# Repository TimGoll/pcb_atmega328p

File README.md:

# PCB Atmega328PB

The board's design is heavily based on the design of the Arduino Uno. All the USB communication stuff was removed. The board is therefore reduced to its bare minimum. The most notable deviation in comparison to the Arduino Uno is that my board uses a 20MHz crystal.

_(The schematic and the PCB I created from this schematic)_

The board is a two layer design with mostly ground planes that are stitched together with multiple vias. All the relevant parts are mounted to the front side.

_(The finished PCB aith the programmer next to it)_

The design of the board works like intended with the one issue, that the ISP connector is mirrored. This however is fixed in the current version in this repository.

## Setup

This board has to be programmed with an ISP connection located on the board. There are different programmers available, I'm using the [Pololu USB AVR Programmer v2.1](https://www.pololu.com/product/3172). The driver package should be installed as it comes with a nice tool to look at the programmer.

A working programmer looks something like this. Do note here that I'm using an external power supply for the MCU here.

If the board is connected, `avrdude` can be used to read the info of the MCU. Use `./avrdude.exe` in the command line while being in the correct folder, for me it is: `C:\Program Files (x86)\Arduino\hardware\tools\avr\bin`.

Use the following command to read the board information:

```sh
./avrdude.exe -C ../etc/avrdude.conf -c stk500 -P COM8 -b 19200 -p m328pb -v
```

`COM8` is used here because it is the programming port of this programmer, `stk500` is the type of the programmer. See [this article](http://www.s6z.de/cms/index.php/arduino/nuetzliches/31-usb-isp-programmer-fuer-atmel-avr-usbasp) for more information on this.

To use an external crystal, the fuses of the board have to be set. The fuse bits can be easily set with the [AVR fuse calculator](https://eleccelerator.com/fusecalc/fusecalc.php?chip=atmega328p&LOW=DE&HIGH=D9&EXTENDED=FF&LOCKBIT=FF). They then have to be flashed to the board. The command is mostly the same, only the `-v` gets replaced by the fuse byte command from the website.

Now the board can be flashed with the desired software. There are different ways to do this, but if the Arduino IDE should be used, a few things have to be set up.

First [MiniCore](https://github.com/MCUdude/MiniCore) has to be added as it features a few more missing AVRs with UI based configurability. The json file link had to be added in the Arduino Settings page as described in the project's readme.

These are the settings that were used here for this specific board setup. It can be easily verified by uploading a simple LED blink sketch.

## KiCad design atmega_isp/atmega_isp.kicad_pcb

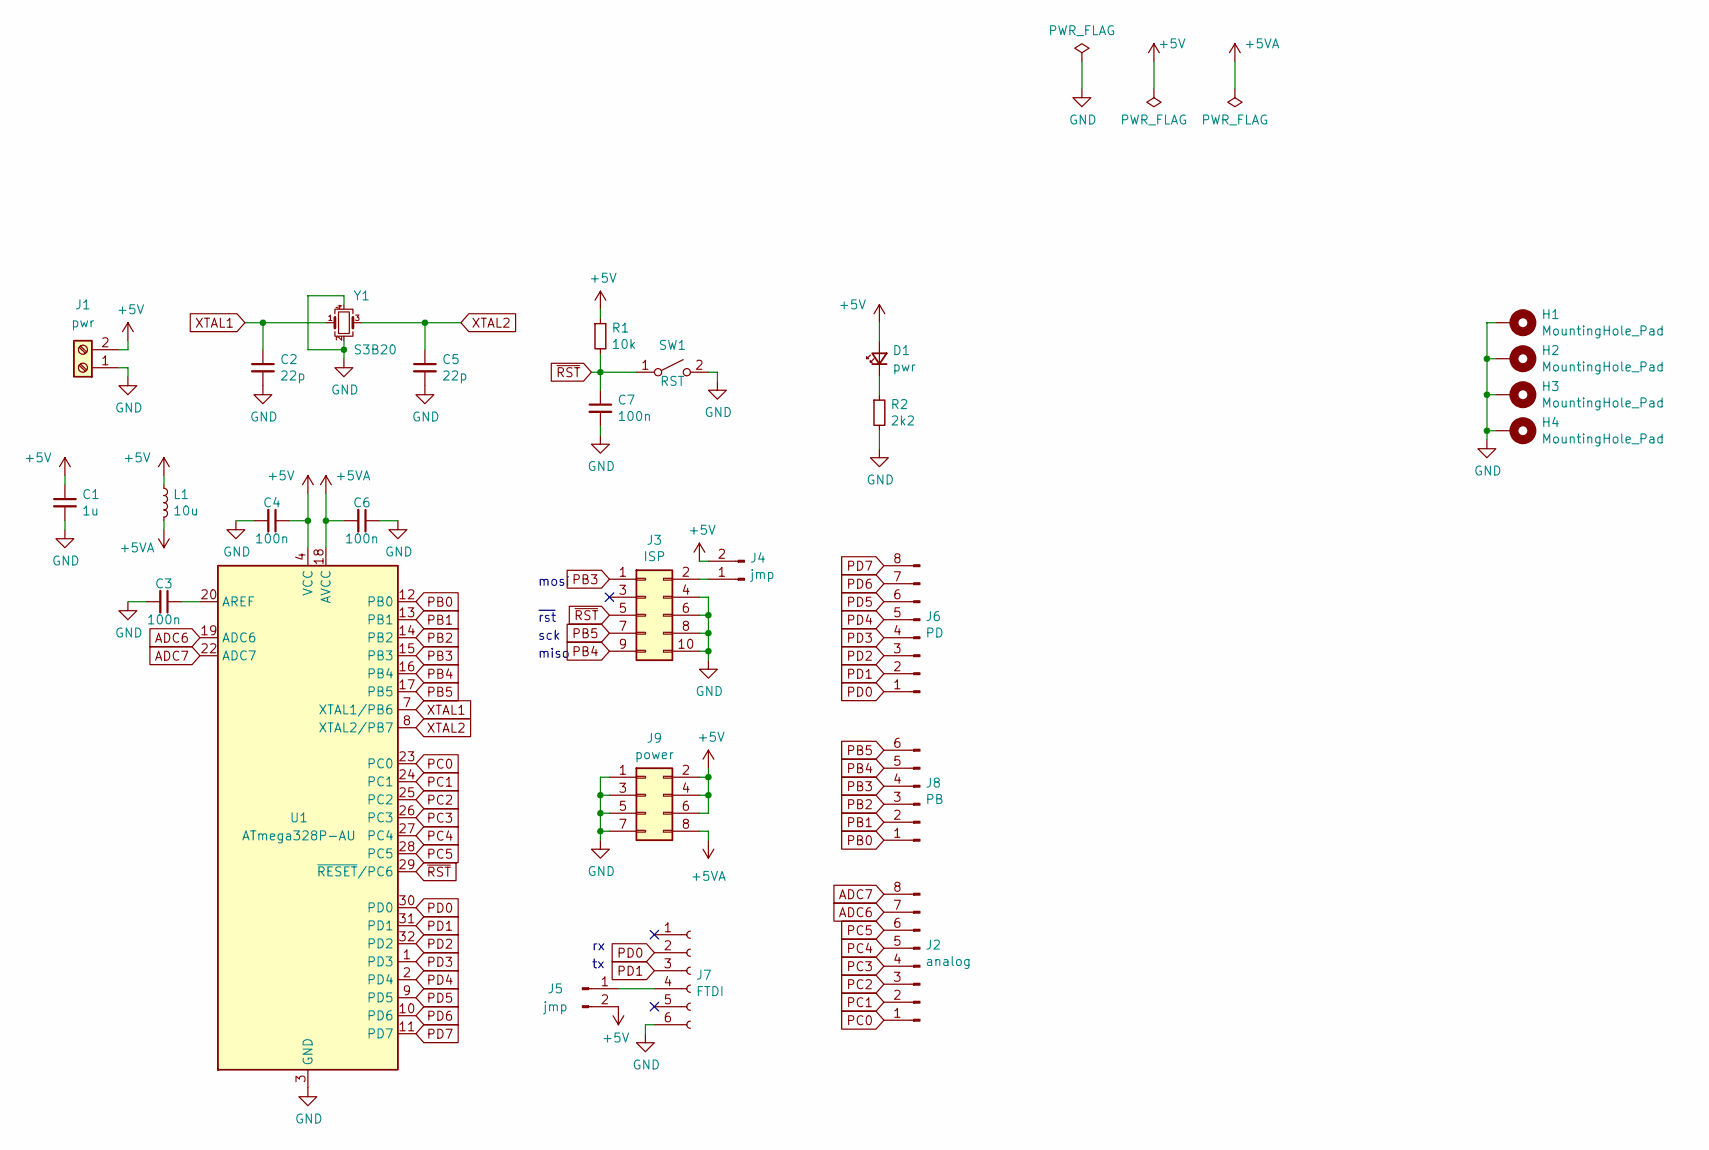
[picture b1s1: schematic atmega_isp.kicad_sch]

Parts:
C1: 1u; C_0805_2012Metric_Pad1.15x1.40mm_HandSolder
C2, C5: 22p; C_0805_2012Metric_Pad1.15x1.40mm_HandSolder
C3, C4, C6, C7: 100n; C_0805_2012Metric_Pad1.15x1.40mm_HandSolder
D1: pwr; LED_0805_2012Metric_Castellated
H1, H2, H3, H4: MountingHole_Pad; MountingHole_4.3mm_M4_Pad_Via
J1: pwr; TerminalBlock_Phoenix_MKDS-1,5-2-5.08_1x02_P5.08mm_Horizont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
J2: analog; PinHeader_1x08_P2.54mm_Vertical
J3: ISP; PinSocket_2x05_P2.54mm_Vertical
J4, J5: jmp; PinHeader_1x02_P2.54mm_Vertical
J6: PD; PinHeader_1x08_P2.54mm_Vertical
J7: FTDI; PinSocket_1x06_P2.54mm_Vertical
J8: PB; PinHeader_1x06_P2.54mm_Vertical
J9: power; PinHeader_2x04_P2.54mm_Vertical
L1: 10u; L_0805_2012Metric_Pad1.15x1.40mm_HandSolder
R1: 10k; R_0805_2012Metric_Pad1.15x1.40mm_HandSolder
R2: 2k2; R_0805_2012Metric_Pad1.15x1.40mm_HandSolder
SW1: RST; SW_Push_1P1T_NO_6x6mm_H9.5mm
U1: ATmega328P-AU; TQFP-32_7x7mm_P0.8mm
Y1: S3B20; Crystal_SMD_3225-4Pin_3.2x2.5mm_HandSoldering

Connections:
+5V: C1.1, C4.1, D1.2 (A), J1.2, J4.2, J5.2, J9.2, J9.4, J9.6, L1.1, R1.1, U1.4 (VCC), U1.6 (VCC)
+5VA: C6.2, J9.8, L1.2, U1.18 (AVCC)
ADC6: J2.7, U1.19 (ADC6)
ADC7: J2.8, U1.22 (ADC7)
GND: C1.2, C2.2, C3.2, C4.2, C5.2, C6.1, C7.2, H1.1, H2.1, H3.1, H4.1, J1.1, J3.4, J3.6, J3.8, J3.10, J7.6, J9.1, J9.3, J9.5, J9.7, R2.2, SW1.2 (B), U1.3 (GND), U1.5 (GND), U1.21 (GND), Y1.2, Y1.4
unnamed: C3.1, U1.20 (AREF)
unnamed: D1.1 (K), R2.1
unnamed: J3.2, J4.1
unnamed: J5.1, J7.4
PB0: J8.1, U1.12 (PB0)
PB1: J8.2, U1.13 (PB1)
PB2: J8.3, U1.14 (PB2)
PB3: J3.1, J8.4, U1.15 (PB3)
PB4: J3.9, J8.5, U1.16 (PB4)
PB5: J3.7, J8.6, U1.17 (PB5)
PC0: J2.1, U1.23 (PC0)
PC1: J2.2, U1.24 (PC1)
PC2: J2.3, U1.25 (PC2)
PC3: J2.4, U1.26 (PC3)
PC4: J2.5, U1.27 (PC4)
PC5: J2.6, U1.28 (PC5)
PD0: J6.1, J7.2, U1.30 (PD0)
PD1: J6.2, J7.3, U1.31 (PD1)
PD2: J6.3, U1.32 (PD2)
PD3: J6.4, U1.1 (PD3)
PD4: J6.5, U1.2 (PD4)
PD5: J6.6, U1.9 (PD5)
PD6: J6.7, U1.10 (PD6)
PD7: J6.8, U1.11 (PD7)
XTAL1: C2.1, U1.7 (XTAL1/PB6), Y1.1
XTAL2: C5.1, U1.8 (XTAL2/PB7), Y1.3
~RST: C7.1, J3.5, R1.2, SW1.1 (A), U1.29 (~RESET/PC6)

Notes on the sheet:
~{rst}
sck
mosi
miso

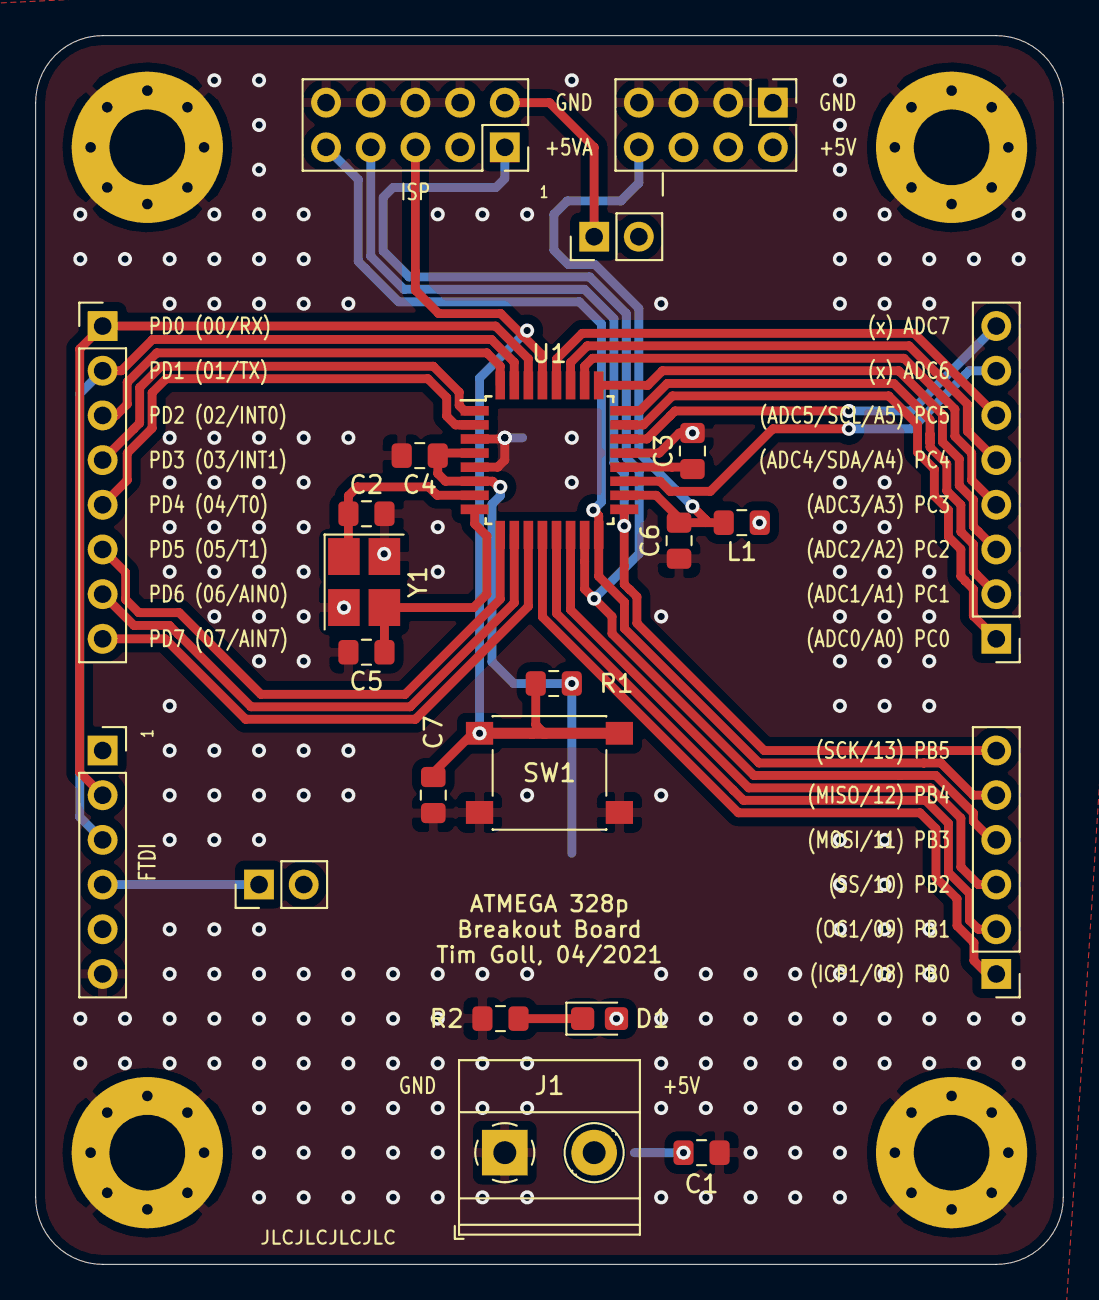
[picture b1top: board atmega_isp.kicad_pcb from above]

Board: 2 copper layers, 58.4 x 69.8 mm, 27 parts (0 on the bottom side), 32 nets.

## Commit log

2021-11-25 added board
2021-11-26 added readme
2022-02-13 kicad 6 update
2022-02-13 added pictures to readme
